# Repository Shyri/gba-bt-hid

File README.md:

## GBA as Bluetooth Gamepad ##
Turn your Game Boy Advance into a Bluetooth Controller :)

### How to use it: ###
After launching the rom the bluetooth module enters discoverable mode. This means you can pair to it from whatever device you are going to use it with (PC, phone, Android TV...). After pairing the program will start sending keys to the device. The device address is stored so next time you launch you just have to press A to automatically connect to that device.

### How it works: ###
The project is basically an ESP32 connected to the GBA through the link port. With the device connected and without any cartridge inserted in the GBA, once the GBA turns on the ESP32 sends a small rom to be loaded in the GBA. This rom is a program made to enable communication between the ESP32 and GBA for both handling bluetooth conneciton and sending the user input to the ESP32 when it is connected to a bluetooth host and act as a gamepad. Unfortunatelly it only works with traditional GBA as I couln't make it work with GBA SP. I think GBA SP just doesn't give enough current.

When turned on the ESP32 (using the code found in [esp32](esp32) peforms a multiboot sequence through the SPI to the GBA sending a rom that the ESP32 has stored in the flash memory. The code for this rom can be found in [gba](gba). Once loaded the ESP32 enables the UART port in the same pins and the rom communicates with the ESP32 using UART through the link port.

This project was tested with ESP-IDF v3.3.2 that you can find here:

https://github.com/espressif/esp-idf/releases

You also will need to install btstack. Commit https://github.com/bluekitchen/btstack/commit/a0a4507b35ea396d076a62a67efb1a5a800c5ff9 is the most recent version that is proved to work in this project.

Just follow the ESP32 environment instructions here

The ESP32 is powered by the 3.3V the GBA gives through the port.
Once the ESP32 is programmed the male link port connector should be wired to it like the following diagram:

The first prototype was made with an Atmega and HC-05:
### Old version prototype: ###

The [gba](gba) contains the code for a GBA program that uses the link port to communicate with a HC-05 bluetooth module using UART (HC-05 flashed with RN-42 firmware, find how to do it in the links at the bottom).

This rom is stored in a W25Q32 flash chip. An Atmega328P performs a multiboot sequence reading from this chip and sending to the GBA through the link port. You can find the Atmega code [here](arduino) (It is actually written for arduino so you'll need to burn arduino's bootloader if you want to use it).

Once multiboot ends, the gba program runs and talks to the HC-05 to handle bluetooth connection, and key presses.

Additional 74XX157 quad 2-input multiplexer makes possible to multiplex SPI to read from the flash chip and send the multiboot, it alternates byte reads from the flash chip and send them to the GBA. Then using hcf4066 switch link port pins are switched from the spi to the HC-05 uart pins.

The whole circuit runs at 3.3V provided by GBA through the link port.

Final version of the circuit includes a 6 pin port that allows to reprogram the atmega if necessary. Also it lets to turn the atmega into a special write mode to reprogram the flash memory. You can find the code for the memory programmer [here](arduino-rom-flasher) it needs to run in a separate board (not arduino due to the large size of the rom to program, I used a Stellaris Launchpad)

There's a KiCad project [here](circuit) that includes this diagram:

### Links that helped me to get this done: ###
ESP32 as a bluetooth Gamepad:
Thanks to the Bluecubemod from Nathan Reeves I learned how to turn ESP32 into a bluetooth gamepad
https://github.com/NathanReeves/BlueCubeMod

HC-05 as bluetooth HID device:

https://www.youtube.com/watch?v=y8PcNbAA6AQ

https://www.youtube.com/watch?v=BBqsVKMYz1I

GBA Multiboot:

http://www.akkit.org/info/gbatek.htm

https://github.com/akkera102/gba_01_multiboot

https://github.com/ataulien/elm-gba-multiboot

https://github.com/cartr/MSMCcable

https://github.com/tangrs/usb-gba-multiboot

https://github.com/MerryMage/gba-multiboot

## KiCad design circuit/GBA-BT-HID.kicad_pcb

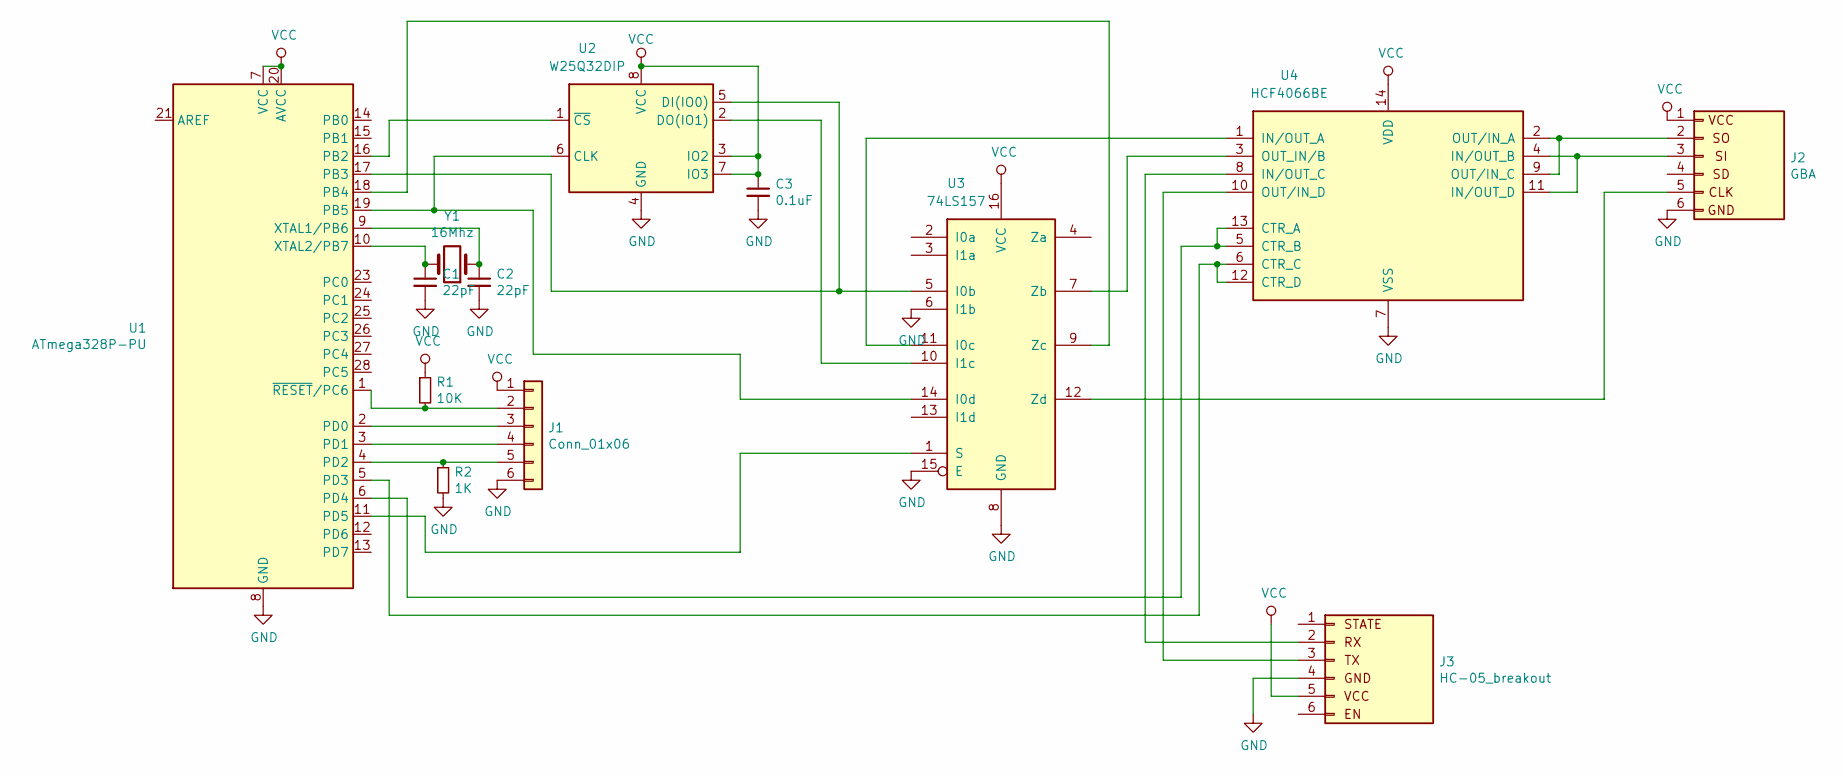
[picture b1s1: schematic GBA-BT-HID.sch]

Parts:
C1, C2: 22pF; C_Disc_D4.7mm_W2.5mm_P5.00mm
C3: 0.1uF; C_Disc_D4.7mm_W2.5mm_P5.00mm
J1: Conn_01x06; PinSocket_1x06_P2.00mm_Vertical
J2: GBA; PinSocket_1x06_P2.00mm_Vertical
J3: HC-05_breakout
R1: 10K; R_Axial_DIN0207_L6.3mm_D2.5mm_P10.16mm_Horizontal
R2: 1K; R_Axial_DIN0207_L6.3mm_D2.5mm_P10.16mm_Horizontal
U1: ATmega328P-PU; DIP-28_W7.62mm
U2: W25Q32DIP; DIP-8_W7.62mm
U3: 74LS157; DIP-16_W7.62mm
U4: HCF4066BE; DIP-14_W7.62mm
Y1: 16Mhz; Resonator-2Pin_W10.0mm_H5.0mm

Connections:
GND: C1.2, C2.2, C3.2, J1.6, J2.6 (GND), J3.4, R2.2, U1.8 (GND), U1.22 (GND), U2.4 (GND), U3.6 (I1b), U3.8 (GND), U3.15 (E), U4.7 (VSS)
unnamed: C1.1, U1.10 (XTAL2/PB7), Y1.2
unnamed: C2.1, U1.9 (XTAL1/PB6), Y1.1
unnamed: J1.2, R1.2, U1.1 (~RESET~/PC6)
unnamed: J1.3, U1.2 (PD0)
unnamed: J1.4, U1.3 (PD1)
unnamed: J1.5, R2.1, U1.4 (PD2)
unnamed: J2.2 (SO), U4.2 (OUT/IN_A), U4.9 (OUT/IN_C)
unnamed: J2.3 (SI), U4.4 (IN/OUT_B), U4.11 (IN/OUT_D)
unnamed: J2.5 (SC), U3.12 (Zd)
unnamed: J3.2, U4.8 (IN/OUT_C)
unnamed: J3.3, U4.10 (OUT/IN_D)
unnamed: U1.5 (PD3), U4.6 (CTR_C), U4.12 (CTR_D)
unnamed: U1.6 (PD4), U4.5 (CTR_B), U4.13 (CTR_A)
unnamed: U1.11 (PD5), U3.1 (S)
unnamed: U1.16 (PB2), U2.1 (~CS)
unnamed: U1.17 (PB3), U2.5 (DI(IO0)), U3.5 (I0b)
unnamed: U1.18 (PB4), U3.9 (Zc)
unnamed: U1.19 (PB5), U2.6 (CLK), U3.14 (I0d)
unnamed: U2.2 (DO(IO1)), U3.10 (I1c)
unnamed: U3.7 (Zb), U4.3 (OUT_IN/B)
unnamed: U3.11 (I0c), U4.1 (IN/OUT_A)
VCC: C3.1, J1.1, J2.1 (Vcc), J3.5, R1.1, U1.7 (VCC), U1.20 (AVCC), U2.3 (IO2), U2.7 (IO3), U2.8 (VCC), U3.16 (VCC), U4.14 (VDD)

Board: 2 copper layers, 13 parts (0 on the bottom side), 23 nets, no tracks yet.

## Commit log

2018-01-12 Initial commit add GBA rom build
2018-12-30 Move gba project into a folder
2018-12-30 Add multiboot program
2018-12-30 Add small test program for hc-05 HID
2019-01-02 Add some modifications to HC-05 test program to know which buttons we want to map
2019-01-02 Change gba rom complation linking to support multiboot
2019-01-03 Add gba rom uart communication to send keys to hc-05
2019-01-20 Improve architecture and clean up everything a bit
2019-01-20 Fix build things and add new rom to multiboot script
2019-01-21 Fix button hold not being sent
2019-01-21 Detect from gba if hc05 is paired to device externally
2019-01-22 GBA Add disconnect feature
2019-01-22 Add multiplexing from SPI to UART when multiboot is done
2019-05-17 Final chagnes (Software)
2019-06-13 Add standalone atmega code
2019-06-13 Add flasher code
2019-06-13 Add circuit diagram project
2019-06-14 Add images for readme
2019-06-14 compress images
2019-06-14 Add back circuit image
2019-09-12 Remove build objects
2019-09-12 Add gitignore for gba project
2019-09-12 Create new ESP32 project
2019-09-14 Port multiboot from arduino code to ESP32
2019-09-21 Add esp32 working example for hid over gatt
2019-11-13 gba binary fix pairing state check
2019-11-13 Add working ESP32 code compatible with HC-05 ready GBA binary
2019-11-14 ESP32 Add connect to last connected device fetaure
2019-12-21 Complete ESP32 implementation
2020-02-22 Clean up ESP32 code
2020-02-22 Move projects to more descriptive folders
2020-04-11 Final cleanup and add some images
2020-04-25 Fix to make it work with esp-idf v3.3.2
